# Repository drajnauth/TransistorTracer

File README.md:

# TransistorTracer
Hardware and software for transistor tracer project.

KiCad PCB files for various versions of the transistor tracer as well as PlatformIO files for the firmware for the Arduino Nano.
The documentation folder contains a pdf version of a PowerPoint presentation regarding the tracer as well as build and operation instructions

A presentation introducing the tracer can be found at https://youtu.be/t6_chWRdSyg.  
This video is a bit dated and some of the information regarding the build, calibration and usage may have changed.

Currently only Hardware version 1 is documented and is working. Other versions are experimental and has not been verified. The software for experimental board versions may not work.

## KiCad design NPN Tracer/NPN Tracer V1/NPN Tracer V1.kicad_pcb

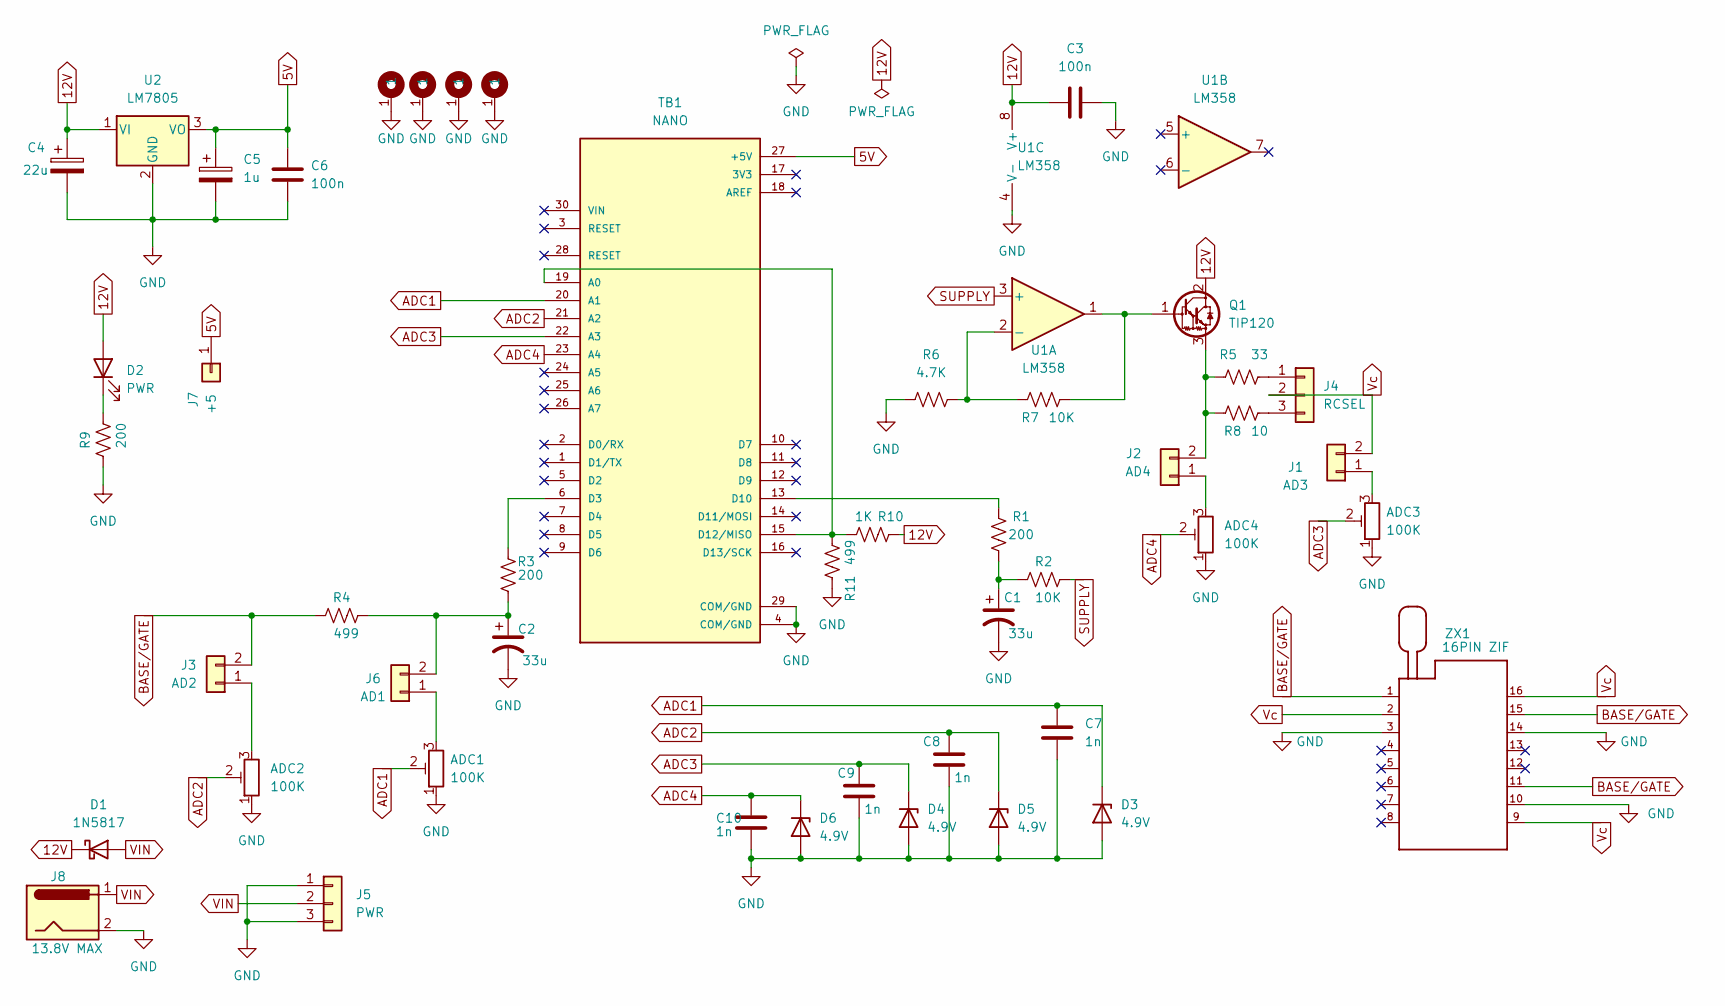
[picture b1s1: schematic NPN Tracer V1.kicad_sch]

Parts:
ADC1, ADC2, ADC3, ADC4: 100K; Potentiometer_Bourns_3296W_Vertical
C1, C2: 33u; CP_Radial_D8.0mm_P2.50mm
C3: 100n; C_1206_3216Metric_Pad1.33x1.80mm_HandSolder
C4: 22u; CP_Radial_D8.0mm_P2.50mm
C5: 1u; CP_Radial_D8.0mm_P2.50mm
C6: 100n; C_1206_3216Metric
C7, C8, C9, C10: 1n; C_1206_3216Metric
D1: 1N5817; D_DO-41_SOD81_P10.16mm_Horizontal
D2: PWR; LED_D3.0mm
D3, D4, D5, D6: 4.9V; D_SOD-323
H1, H2, H3, H4: MountingHole; MountingHole_3.2mm_M3_ISO7380_Pad_TopBottom
J1: AD3; PinHeader_1x02_P2.54mm_Vertical
J2: AD4; PinHeader_1x02_P2.54mm_Vertical
J3: AD2; PinHeader_1x02_P2.54mm_Vertical
J4: RCSEL; PinHeader_1x03_P2.54mm_Vertical
J5: PWR; PinHeader_1x03_P2.54mm_Vertical
J6: AD1; PinHeader_1x02_P2.54mm_Vertical
J7: +5; PinHeader_1x01_P2.54mm_Vertical
J8: 13.8V MAX; BarrelJack_GCT_DCJ200-10-A_Horizontal
Q1: TIP120; TO-220-3_Vertical
R1, R3: 200; R_Axial_DIN0204_L3.6mm_D1.6mm_P5.08mm_Vertical
R2, R7: 10K; R_1206_3216Metric_Pad1.30x1.75mm_HandSolder
R4: 499; R_Axial_DIN0204_L3.6mm_D1.6mm_P5.08mm_Vertical
R5: 33; R_Axial_DIN0516_L15.5mm_D5.0mm_P7.62mm_Vertical
R6: 4.7K; R_1206_3216Metric_Pad1.30x1.75mm_HandSolder
R8: 10; R_Axial_DIN0516_L15.5mm_D5.0mm_P7.62mm_Vertical
R9: 200; R_1206_3216Metric_Pad1.30x1.75mm_HandSolder
R10: 1K; R_1206_3216Metric_Pad1.30x1.75mm_HandSolder
R11: 499; R_1206_3216Metric_Pad1.30x1.75mm_HandSolder
TB1: NANO; SHIELD_ARDUINO_NANO
U1: LM358; DIP-8_W7.62mm_Socket
U2: LM7805; TO-220-3_Vertical
ZX1: 16PIN ZIF; 16Pin ZIF; MPN 216-3340-00-0602J

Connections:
5V: C5.1, C6.1, J7.1, TB1.27 (+5V), U2.3 (VO)
12V: C3.1, C4.1, D1.1 (K), D2.2 (A), Q1.2 (C), R10.2, U1.8 (V+), U2.1 (VI)
ADC1: ADC1.2, C7.1, D3.1 (K), TB1.20 (A1)
ADC2: ADC2.2, C8.1, D5.1 (K), TB1.21 (A2)
ADC3: ADC3.2, C9.1, D4.1 (K), TB1.22 (A3)
ADC4: ADC4.2, C10.1, D6.1 (K), TB1.23 (A4)
BASE/GATE: J3.2, R4.1, ZX1.1, ZX1.11, ZX1.15
GND: ADC1.1, ADC2.1, ADC3.1, ADC4.1, C1.2, C2.2, C3.2, C4.2, C5.2, C6.2, C7.2, C8.2, C9.2, C10.2, D3.2 (A), D4.2 (A), D5.2 (A), D6.2 (A), H1.1, H2.1, H3.1, H4.1, J5.1, J5.3, J8.2, R6.1, R9.1, R11.2, TB1.4 (COM/GND), TB1.29 (COM/GND), U1.4 (V-), U2.2 (GND), ZX1.3, ZX1.10, ZX1.14
unnamed: ADC1.3, J6.1
unnamed: ADC2.3, J3.1
unnamed: ADC3.3, J1.1
unnamed: ADC4.3, J2.1
unnamed: C1.1, R1.1, R2.1
unnamed: C2.1, J6.2, R3.1, R4.2
unnamed: D2.1 (K), R9.2
unnamed: J2.2, Q1.3 (E), R5.1, R8.1
unnamed: J4.1, R5.2
unnamed: J4.3, R8.2
unnamed: Q1.1 (B), R7.2, U1.1
unnamed: R1.2, TB1.13 (D10)
unnamed: R3.2, TB1.6 (D3)
unnamed: R6.2, R7.1, U1.2 (-)
unnamed: R10.1, R11.1, TB1.15 (D12/MISO), TB1.19 (A0)
SUPPLY: R2.2, U1.3 (+)
VIN: D1.2 (A), J5.2, J8.1
Vc: J1.2, J4.2, ZX1.2, ZX1.9, ZX1.16

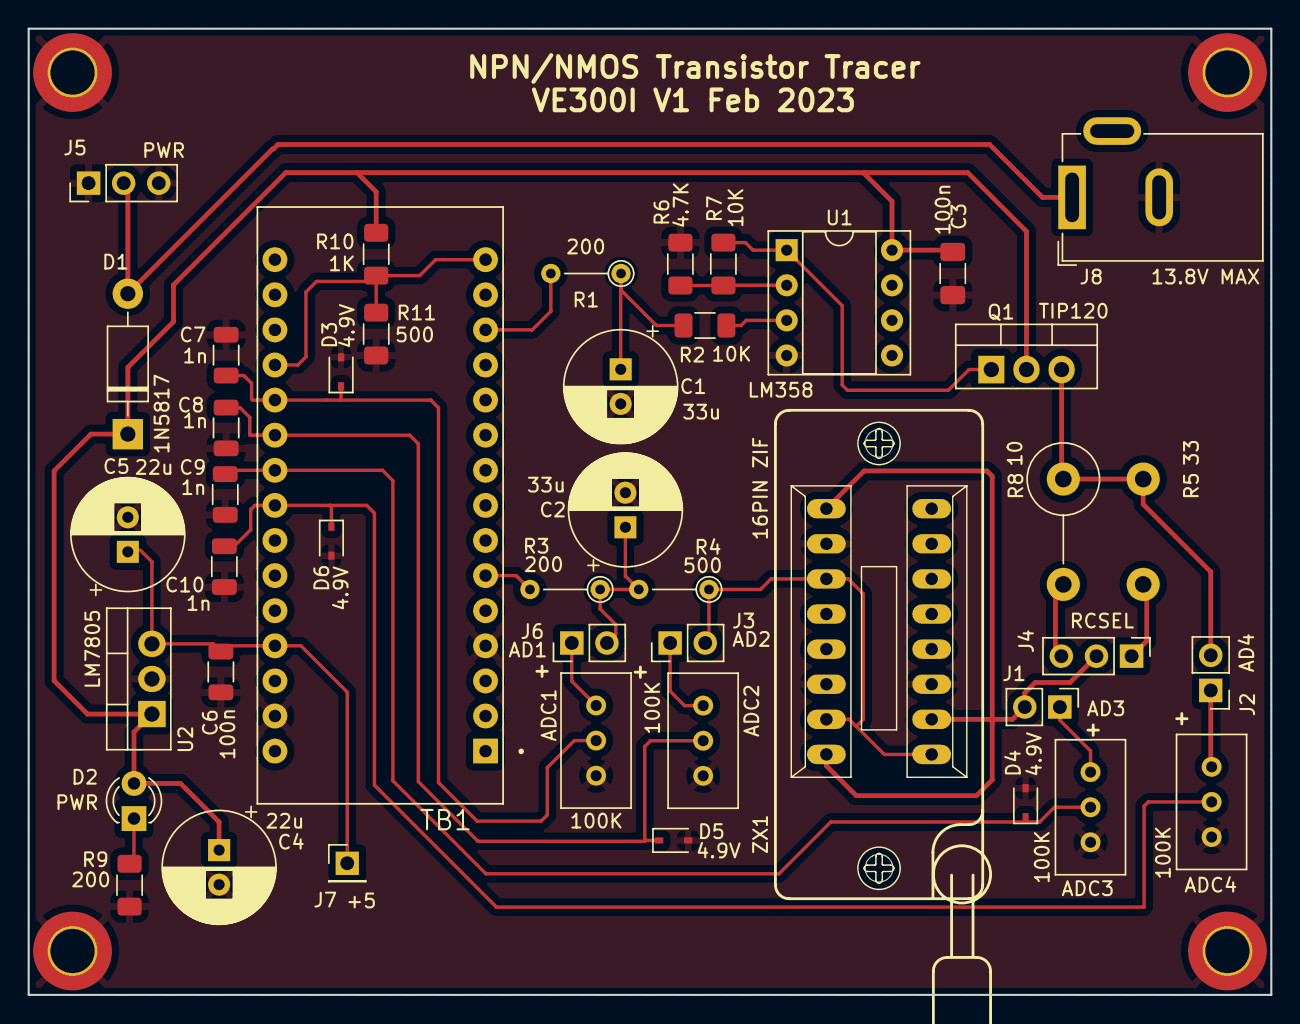
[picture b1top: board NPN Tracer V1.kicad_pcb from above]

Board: 2 copper layers, 89.9 x 69.9 mm, 48 parts (1 on the bottom side), 26 nets.

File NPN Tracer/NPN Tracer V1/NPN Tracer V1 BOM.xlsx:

Component Count: | 44 |  |  | Note: Many of the resistor values can be changed except for PWM resistors (R1 &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
Ref | Qnty | Value | Cmp name | Notes | Footprint | Description | Vendor
ADC1, ADC2, ADC3, ADC4, | 4 | 10K | R_Potentiometer_Trim | Error. Use 100K Pots | Potentiometer_THT:Potentiometer_Bourns_3296W_Vertical | Trim-potentiometer
C1, C2, | 2 | 33u | C_Polarized_US |  | Capacitor_THT:CP_Radial_D8.0mm_P2.50mm | Polarized capacitor, US symbol
C3, | 1 | 100n | C |  | Capacitor_SMD:C_1206_3216Metric_Pad1.33x1.80mm_HandSolder | Unpolarized capacitor
C4, | 1 | 22u | C_Polarized | This is for voltage regulator. Anything around 10 or 20uF is adaquate. | Capacitor_THT:CP_Radial_D8.0mm_P2.50mm | Polarized capacitor
C4 | 1 | 1u | C_Polarized | This is for voltage regulator. Anything around 1uF is adaquate. | Capacitor_THT:CP_Radial_D8.0mm_P2.50mm | Polarized capacitor
C6, | 1 | 100n | C |  | Capacitor_SMD:C_1206_3216Metric | Unpolarized capacitor
C7, C8, C9, C10, | 4 | 1n | C | Optional. Used to reduce noise on ADC line. If ADC values are noisy, then add c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 | Capacitor_SMD:C_1206_3216Metric | Unpolarized capacitor
D1, | 1 | 1N5817 | 1N5817 | Use any Shottky Diode with low voltage drop and high current. Need about 1-2A | Diode_THT:D_DO-41_SOD81_P10.16mm_Horizontal | 20V 1A Schottky Barrier Rectifier Diode, DO-41
D2, | 1 | PWR | LED | Use any LED with 3mm Footprint with max current of 60mA | LED_THT:LED_D3.0mm | Light emitting diode
D3, D4, D5, D6, | 4 | 4.9V | D_Zener | Optional. Can be omitted. Used to protect Arduino should >5V fed to ADC pins. | Diode_SMD:D_SOD-323 | Zener diode
J1, | 1 | AD3 | Conn_01x02 |  | Connector_PinHeader_2.54mm:PinHeader_1x02_P2.54mm_Vertical | Generic connector, single row, 01x02, script generated (kicad-library-utils/sch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
J2, | 1 | AD4 | Conn_01x02 |  | Connector_PinHeader_2.54mm:PinHeader_1x02_P2.54mm_Vertical | Generic connector, single row, 01x02, script generated (kicad-library-utils/sch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
J3, | 1 | AD2 | Conn_01x02 |  | Connector_PinHeader_2.54mm:PinHeader_1x02_P2.54mm_Vertical | Generic connector, single row, 01x02, script generated (kicad-library-utils/sch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
J4, | 1 | RCSEL | Conn_01x03 |  | Connector_PinHeader_2.54mm:PinHeader_1x03_P2.54mm_Vertical | Generic connector, single row, 01x03, script generated (kicad-library-utils/sch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
J5, | 1 | PWR | Conn_01x03 |  | Connector_PinHeader_2.54mm:PinHeader_1x03_P2.54mm_Vertical | Generic connector, single row, 01x03, script generated (kicad-library-utils/sch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
J6, | 1 | AD1 | Conn_01x02 |  | Connector_PinHeader_2.54mm:PinHeader_1x02_P2.54mm_Vertical | Generic connector, single row, 01x02, script generated (kicad-library-utils/sch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
J7, | 1 | 5 | Conn_01x01 |  | Connector_PinHeader_2.54mm:PinHeader_1x01_P2.54mm_Vertical | Generic connector, single row, 01x01, script generated (kicad-library-utils/sch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
J8, | 1 | 13.8V MAX | Barrel_Jack | J5/PWR connector can be used instead. Middle pin is power. | Connector_BarrelJack:BarrelJack_GCT_DCJ200-10-A_Horizontal | DC Barrel Jack
Q1, | 1 | TIP120 | TIP120 | Can use any high current transistor. TIP122, 2SC5706 with same TO-220 footprint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 | Package_TO_SOT_THT:TO-220-3_Vertical | 5A Ic, 60V Vce, Silicon Darlington Power NPN Transistor, TO-220
R1, R3, | 2 | 200 | R_US |  | Resistor_THT:R_Axial_DIN0204_L3.6mm_D1.6mm_P5.08mm_Vertical | Resistor, US symbol
R10, | 1 | 1K | R_US | Measure the actual value with VOM and enter it during calibration | Resistor_SMD:R_1206_3216Metric_Pad1.30x1.75mm_HandSolder | Resistor, US symbol
R11, | 1 | 499 | R_US | Anything below 523R and around 500R. E.g. 475, 487,499, 511, 523. Measure the a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 | Resistor_SMD:R_1206_3216Metric_Pad1.30x1.75mm_HandSolder | Resistor, US symbol
R2, R7, | 2 | 10K | R_US | R2 can be anything around 10K. R7 MUST be 10K | Resistor_SMD:R_1206_3216Metric_Pad1.30x1.75mm_HandSolder | Resistor, US symbol
R4, | 1 | 499 | R_US | Use resistor below 500R. I used 462. This limits how much current delivered to 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 | Resistor_THT:R_Axial_DIN0204_L3.6mm_D1.6mm_P5.08mm_Vertical | Resistor, US symbol
R5, | 1 | 33 | R_US | 2 Watt resistor. Measure the actual value with VOM and enter it during calibrat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 | Resistor_THT:R_Axial_DIN0516_L15.5mm_D5.0mm_P7.62mm_Vertical | Resistor, US symbol
R6, | 1 | 4.7K | R_US | This resistor sets the gain of the LM358. 4.7K seems to be ok. Might be a littl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 | Resistor_SMD:R_1206_3216Metric_Pad1.30x1.75mm_HandSolder | Resistor, US symbol
R8, | 1 | 10 | R_US | 2 Watt resistor. Measure the actual value with VOM and enter it during calibrat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 | Resistor_THT:R_Axial_DIN0516_L15.5mm_D5.0mm_P7.62mm_Vertical | Resistor, US symbol
R9, | 1 | 200 | R_US |  | Resistor_SMD:R_1206_3216Metric_Pad1.30x1.75mm_HandSolder | Resistor, US symbol
TB1, | 1 | NANO | ARDUINO_NANO |  | SHIELD_ARDUINO_NANO
U1, | 1 | LM358 | LM358 |  | Package_DIP:DIP-8_W7.62mm_Socket | Low-Power, Dual Operational Amplifiers, DIP-8/SOIC-8/TO-99-8
U2, | 1 | LM7805 | LM7805_TO220 |  | Package_TO_SOT_THT:TO-220-3_Vertical | Positive 1A 35V Linear Regulator, Fixed Output 5V, TO-220
ZX1, | 1 | 16PIN ZIF | 16Pin ZIF |  | Custom_RF:16Pin ZIF

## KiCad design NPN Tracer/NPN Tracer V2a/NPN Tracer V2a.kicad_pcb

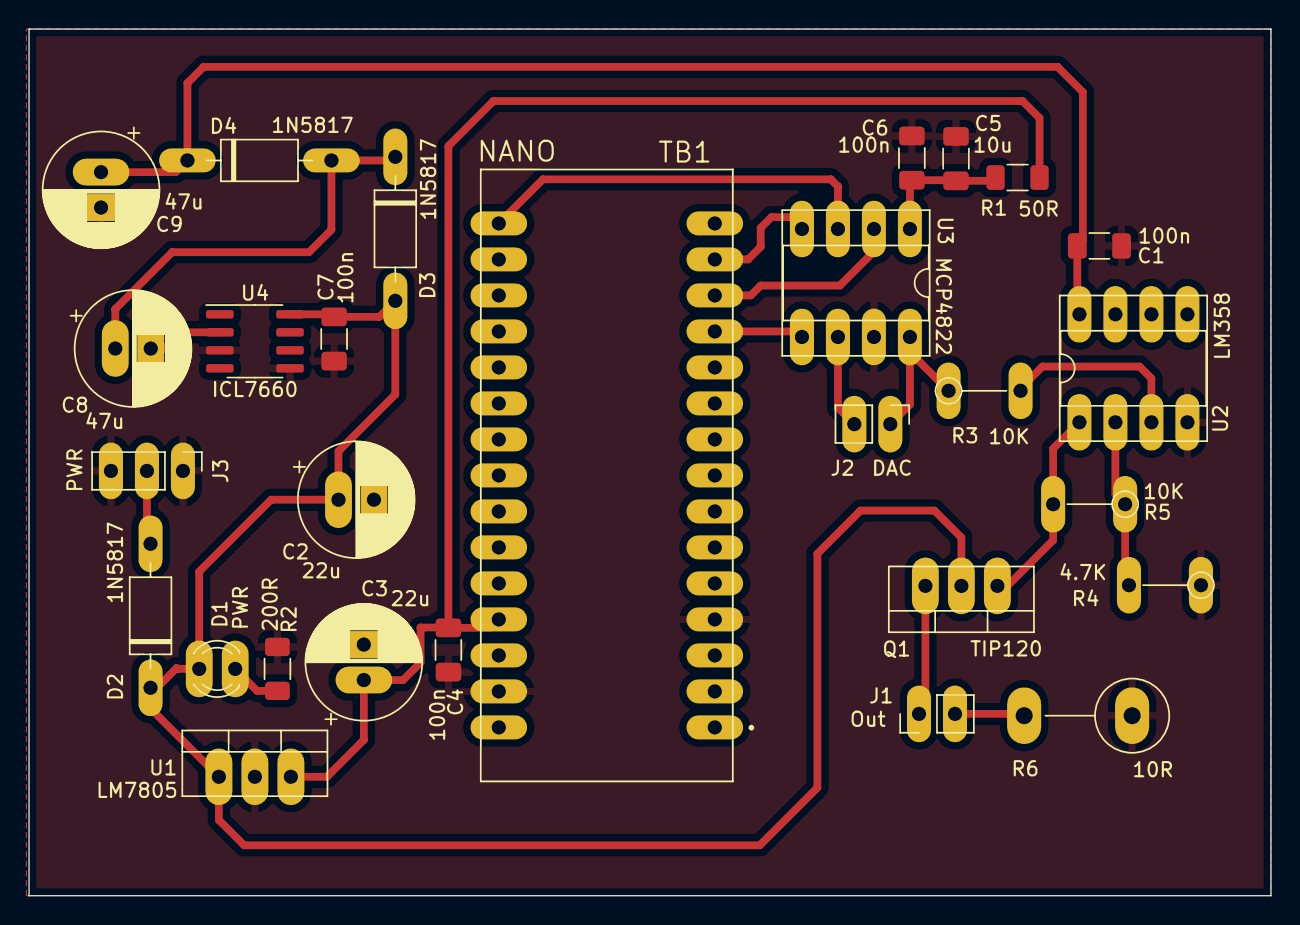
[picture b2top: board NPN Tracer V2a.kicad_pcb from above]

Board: 2 copper layers, 87.6 x 61.2 mm, 28 parts (0 on the bottom side), 20 nets.

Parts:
C1, C4, C6, C7: 100n; C_1206_3216Metric_Pad1.33x1.80mm_HandSolder
C2, C3: 22u; CP_Radial_D8.0mm_P2.50mm
C5: 10u; C_1206_3216Metric_Pad1.33x1.80mm_HandSolder
C8, C9: 47u; CP_Radial_D8.0mm_P2.50mm
D1: PWR; LED_D3.0mm
D2, D3, D4: 1N5817; D_DO-41_SOD81_P10.16mm_Horizontal
J1: Out; PinHeader_1x02_P2.54mm_Vertical
J2: DAC; PinHeader_1x02_P2.54mm_Vertical
J3: PWR; PinHeader_1x03_P2.54mm_Vertical
Q1: TIP120; TO-220-3_Vertical
R1: 50R; R_1206_3216Metric_Pad1.30x1.75mm_HandSolder
R2: 200R; R_1206_3216Metric_Pad1.30x1.75mm_HandSolder
R3, R5: 10K; R_Axial_DIN0204_L3.6mm_D1.6mm_P5.08mm_Vertical
R4: 4.7K; R_Axial_DIN0204_L3.6mm_D1.6mm_P5.08mm_Vertical
R6: 10R; R_Axial_DIN0516_L15.5mm_D5.0mm_P7.62mm_Vertical
TB1: NANO; SHIELD_ARDUINO_NANO
U1: LM7805; TO-220-3_Vertical
U2: LM358; DIP-8_W7.62mm_Socket
U3: MCP4822; DIP-8_W7.62mm_Socket
U4: ICL7660; SOIC-8_3.9x4.9mm_P1.27mm

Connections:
5V: C3.1, C4.2, R1.2, TB1.27 (+5V), U1.3 (VO)
12V: C2.1, C7.2, D1.2 (A), D2.1 (K), D3.2 (A), Q1.2 (C), U1.1 (VI), U4.8 (V+)
24V: C1.1, C9.1, D4.1 (K), U2.8 (V+)
GND: C1.2, C2.2, C3.2, C4.1, C5.1, C6.1, C7.1, C9.2, J3.1, J3.3, R2.1, R4.1, R6.1, TB1.4 (COM/GND), TB1.29 (COM/GND), U1.2 (GND), U2.4 (V-), U3.7 (Vss), U4.3 (GND), U4.5 (VOUT)
unnamed: C5.2, C6.2, R1.1, U3.1 (Vdd)
unnamed: C8.1, D3.1 (K), D4.2 (A)
unnamed: C8.2, U4.2 (CAP+)
unnamed: D1.1 (K), R2.2
unnamed: J1.1, Q1.3 (E)
unnamed: J1.2, R6.2
unnamed: J2.1, R3.1, U3.8 (VA)
unnamed: J2.2, U3.6 (VB)
unnamed: Q1.1 (B), R5.2, U2.1
unnamed: R3.2, U2.3 (+)
unnamed: R4.2, R5.1, U2.2 (-)
unnamed: TB1.12 (D9), U3.5 (~LDAC)
unnamed: TB1.13 (D10), U3.2 (~CS)
unnamed: TB1.14 (D11/MOSI), U3.4 (SDI)
unnamed: TB1.16 (D13/SCK), U3.3 (SCK)
VIN: D2.2 (A), J3.2

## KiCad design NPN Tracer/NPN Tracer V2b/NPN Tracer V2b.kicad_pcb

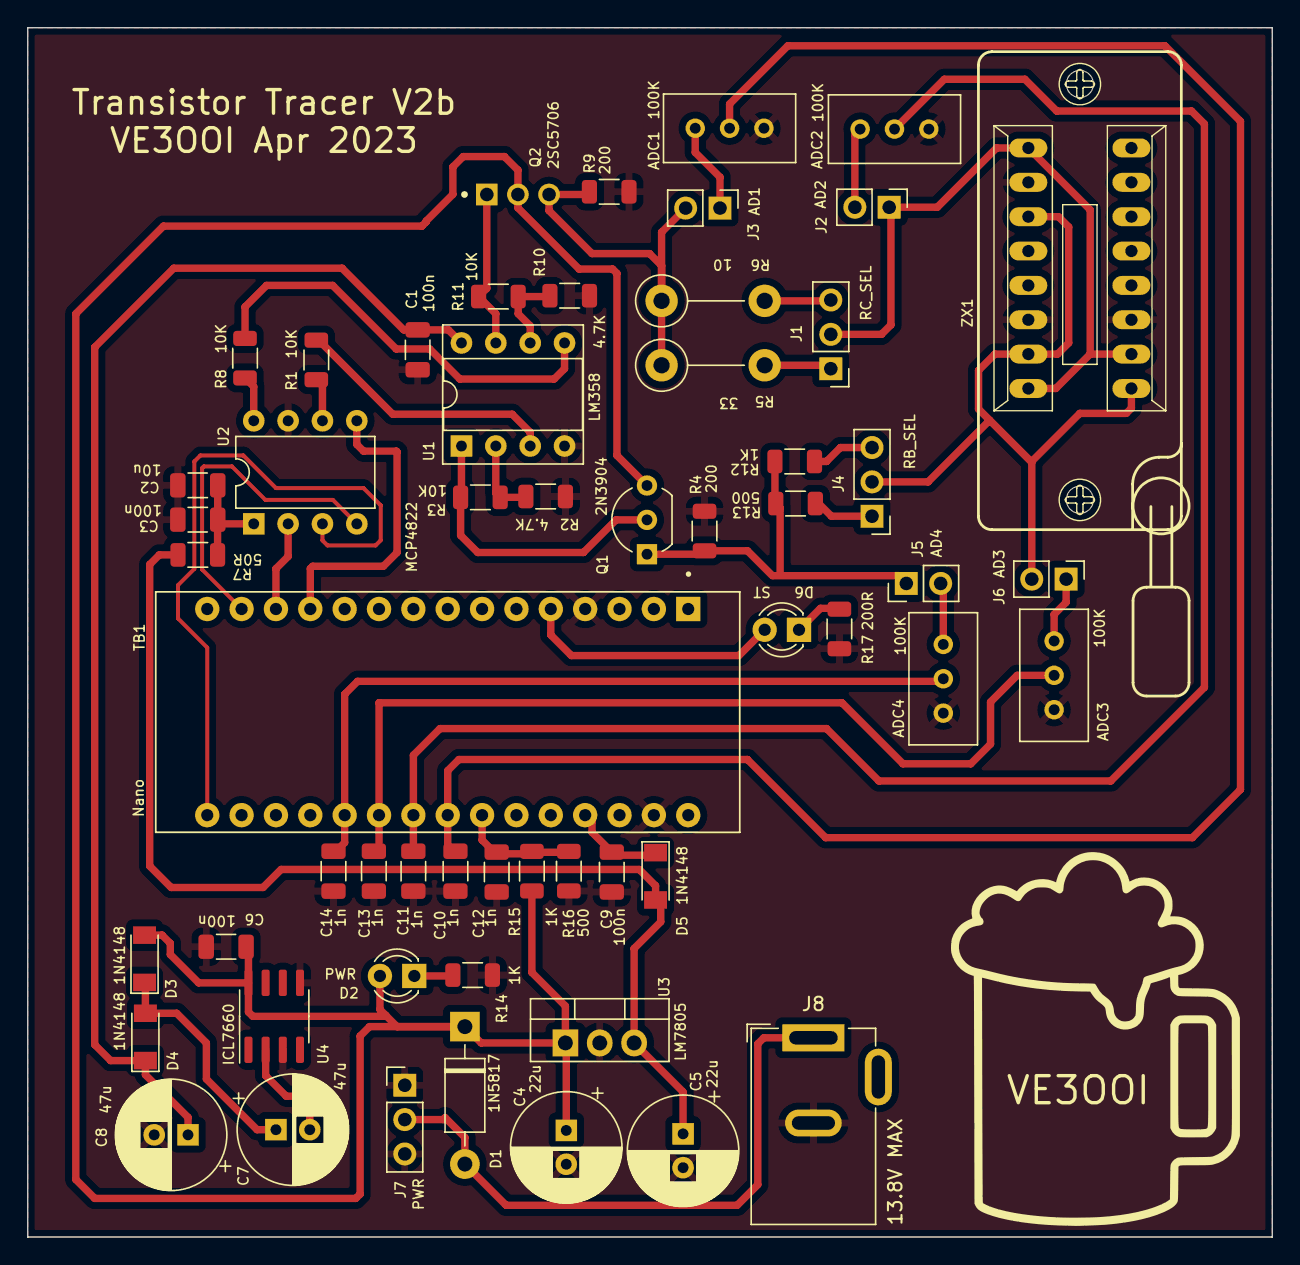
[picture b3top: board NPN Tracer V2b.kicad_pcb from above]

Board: 2 copper layers, 92.0 x 89.4 mm, 57 parts (0 on the bottom side), 41 nets.

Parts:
ADC1, ADC2, ADC3, ADC4: 100K; Potentiometer_Bourns_3296W_Vertical
C1, C3, C6, C9: 100n; C_1206_3216Metric
C2: 10u; C_1206_3216Metric
C4, C5: 22u; CP_Radial_D8.0mm_P2.50mm
C7, C8: 47u; CP_Radial_D8.0mm_P2.50mm
C10, C11, C12, C13, C14: 1n; C_1206_3216Metric
D1: 1N5817; D_DO-41_SOD81_P10.16mm_Horizontal
D2: PWR; LED_D3.0mm
D3, D4, D5: 1N4148; D_MiniMELF
D6: ST; LED_D3.0mm
J1: RC_SEL; PinHeader_1x03_P2.54mm_Vertical
J2: AD2; PinHeader_1x02_P2.54mm_Vertical
J3: AD1; PinHeader_1x02_P2.54mm_Vertical
J4: RB_SEL; PinHeader_1x03_P2.54mm_Vertical
J5: AD4; PinHeader_1x02_P2.54mm_Vertical
J6: AD3; PinHeader_1x02_P2.54mm_Vertical
J7: PWR; PinHeader_1x03_P2.54mm_Vertical
J8: 13.8V MAX; BarrelJack_GCT_DCJ200-10-A_Horizontal
Q1: 2N3904; TO-92_Inline_Wide
Q2: 2SC5706
R1, R3, R8, R11: 10K; R_1206_3216Metric
R2, R10: 4.7K; R_1206_3216Metric
R4, R9: 200; R_1206_3216Metric
R5: 33; R_Axial_DIN0411_L9.9mm_D3.6mm_P7.62mm_Vertical
R6: 10; R_Axial_DIN0411_L9.9mm_D3.6mm_P7.62mm_Vertical
R7: 50R; R_1206_3216Metric
R12, R14, R15: 1K; R_1206_3216Metric
R13, R16: 500; R_1206_3216Metric
R17: 200R; R_1206_3216Metric
TB1: Nano; SHIELD_ARDUINO_NANO
U1: LM358; DIP-8_W7.62mm_Socket
U2: MCP4822; DIP-8_W7.62mm
U3: LM7805; TO-220-3_Vertical
U4: ICL7660; SOIC-8_3.9x4.9mm_P1.27mm
ZX1: 16PIN ZIF; 16Pin ZIF

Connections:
5V: C5.1, D5.2 (A), R7.2, U3.3 (VO)
12V: C4.1, C6.2, D1.1 (K), D2.2 (A), D3.2 (A), Q1.3 (C), Q2.2 (C), R15.2, U3.1 (VI), U4.8 (V+)
24V: C1.1, C8.1, D4.1 (K), U1.8 (V+)
ADC1: ADC4.2, C14.1, TB1.20 (A1)
ADC2: ADC3.2, C13.1, TB1.21 (A2)
ADC3: ADC2.2, C11.1, TB1.22 (A3)
ADC4: ADC1.2, C10.1, TB1.23 (A4)
BASE/GATE: J4.2, J6.2, ZX1.1, ZX1.11, ZX1.15
COLLECTOR/DRAIN: J1.2, J2.1, ZX1.2, ZX1.9, ZX1.16
CS: TB1.13 (D10), U2.2 (~CS)
DacPower: C2.2, C3.2, R7.1, U2.1 (Vdd)
GND: ADC1.1, ADC2.1, ADC3.1, ADC4.1, C1.2, C2.1, C3.1, C4.2, C5.2, C6.1, C8.2, C9.2, C10.2, C11.2, C12.2, C13.2, C14.2, J7.1, J7.3, J8.2, R2.1, R4.1, R9.1, R10.1, R14.1, R16.2, R17.1, TB1.4 (COM/GND), TB1.29 (COM/GND), U1.4 (V-), U2.7 (Vss), U3.2 (GND), U4.3 (GND), U4.5 (VOUT), ZX1.3, ZX1.10, ZX1.14
LDAC: TB1.12 (D9), U2.5 (~LDAC)
unnamed: ADC1.3, J3.1
unnamed: ADC2.3, J2.2
unnamed: ADC3.3, J6.1
unnamed: ADC4.3, J5.2
unnamed: C7.1, D3.1 (K), D4.2 (A)
unnamed: C7.2, U4.2 (CAP+)
unnamed: C12.1, R15.1, R16.1, TB1.24 (A5)
unnamed: D2.1 (K), R14.2
unnamed: D6.1 (K), R17.2
unnamed: D6.2 (A), TB1.5 (D2)
unnamed: J1.1, R5.2
unnamed: J1.3, R6.2
unnamed: J4.1, R13.1
unnamed: J4.3, R12.1
unnamed: Q1.2 (B), R3.2, U1.1
unnamed: Q2.1 (B), R11.2, U1.7
unnamed: R1.1, U2.6 (VB)
unnamed: R1.2, U1.3 (+)
unnamed: R2.2, R3.1, U1.2 (-)
unnamed: R8.1, U2.8 (VA)
unnamed: R8.2, U1.5 (+)
unnamed: R10.2, R11.1, U1.6 (-)
SCK: TB1.16 (D13/SCK), U2.3 (SCK)
SDI: TB1.14 (D11/MOSI), U2.4 (SDI)
VB_OUT: J5.1, Q1.1 (E), R4.2, R12.2, R13.2
VC_OUT: J3.2, Q2.3 (E), R5.1, R6.1, R9.2
VIN: D1.2 (A), J7.2, J8.1
uCPower: C9.1, D5.1 (K), TB1.27 (+5V)

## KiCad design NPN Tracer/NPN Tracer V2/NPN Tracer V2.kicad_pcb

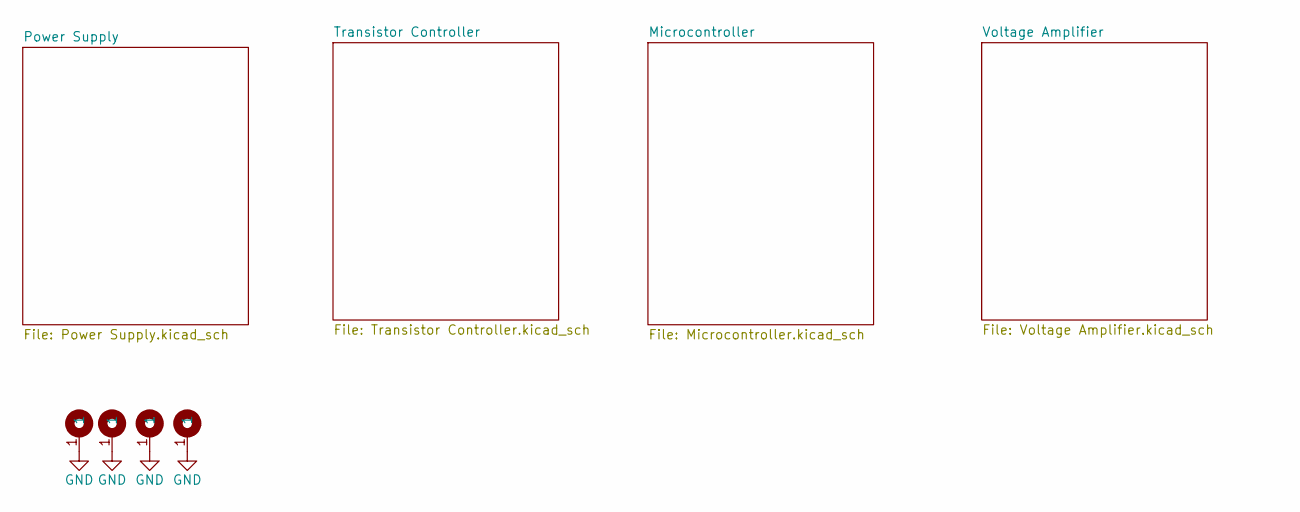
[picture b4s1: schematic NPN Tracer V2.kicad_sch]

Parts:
H1, H2, H3, H4: MountingHole; MountingHole_3.2mm_M3_ISO7380_Pad_TopBottom

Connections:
GND: H1.1, H2.1, H3.1, H4.1; also elsewhere on the board

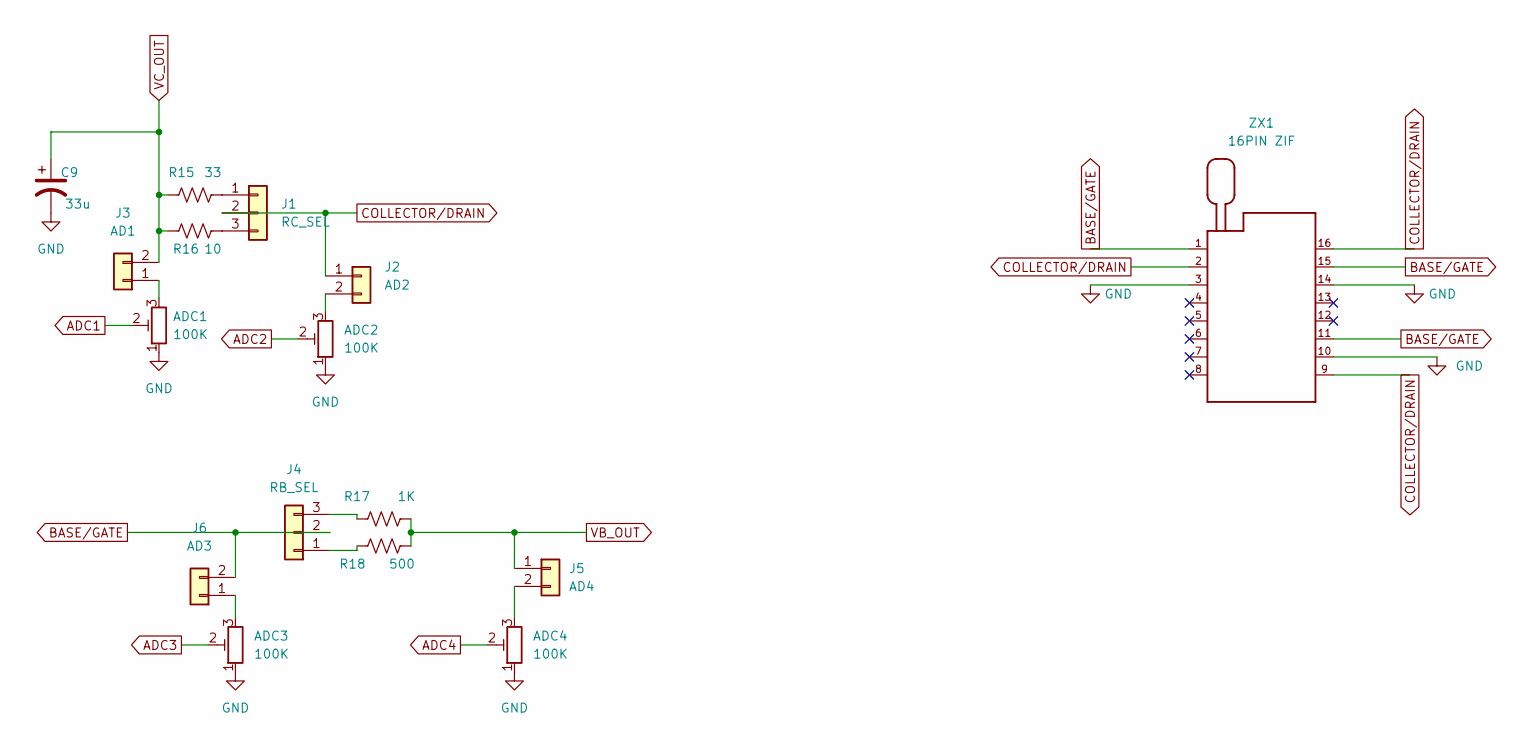
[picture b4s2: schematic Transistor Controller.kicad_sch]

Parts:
ADC1, ADC2, ADC3, ADC4: 100K; Potentiometer_Bourns_3296W_Vertical
C9: 33u; CP_Radial_D8.0mm_P2.50mm
J1: RC_SEL; PinHeader_1x03_P2.54mm_Vertical
J2: AD2; PinHeader_1x02_P2.54mm_Vertical
J3: AD1; PinHeader_1x02_P2.54mm_Vertical
J4: RB_SEL; PinHeader_1x03_P2.54mm_Vertical
J5: AD4; PinHeader_1x02_P2.54mm_Vertical
J6: AD3; PinHeader_1x02_P2.54mm_Vertical
R15: 33; R_Axial_DIN0411_L9.9mm_D3.6mm_P7.62mm_Vertical
R16: 10; R_Axial_DIN0411_L9.9mm_D3.6mm_P7.62mm_Vertical
R17: 1K; R_1206_3216Metric
R18: 500; R_1206_3216Metric
ZX1: 16PIN ZIF; 16Pin ZIF; MPN 216-3340-00-0602J

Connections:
ADC1: ADC1.2; also elsewhere on the board
ADC2: ADC2.2; also elsewhere on the board
ADC3: ADC3.2; also elsewhere on the board
ADC4: ADC4.2; also elsewhere on the board
BASE/GATE: J4.2, J6.2, ZX1.1, ZX1.11, ZX1.15
COLLECTOR/DRAIN: J1.2, J2.1, ZX1.2, ZX1.9, ZX1.16
GND: ADC1.1, ADC2.1, ADC3.1, ADC4.1, C9.2, ZX1.3, ZX1.10, ZX1.14; also elsewhere on the board
unnamed: ADC1.3, J3.1
unnamed: ADC2.3, J2.2
unnamed: ADC3.3, J6.1
unnamed: ADC4.3, J5.2
unnamed: J1.1, R15.2
unnamed: J1.3, R16.2
unnamed: J4.1, R18.1
unnamed: J4.3, R17.1
VB_OUT: J5.1, R17.2, R18.2; also elsewhere on the board
VC_OUT: C9.1, J3.2, R15.1, R16.1; also elsewhere on the board

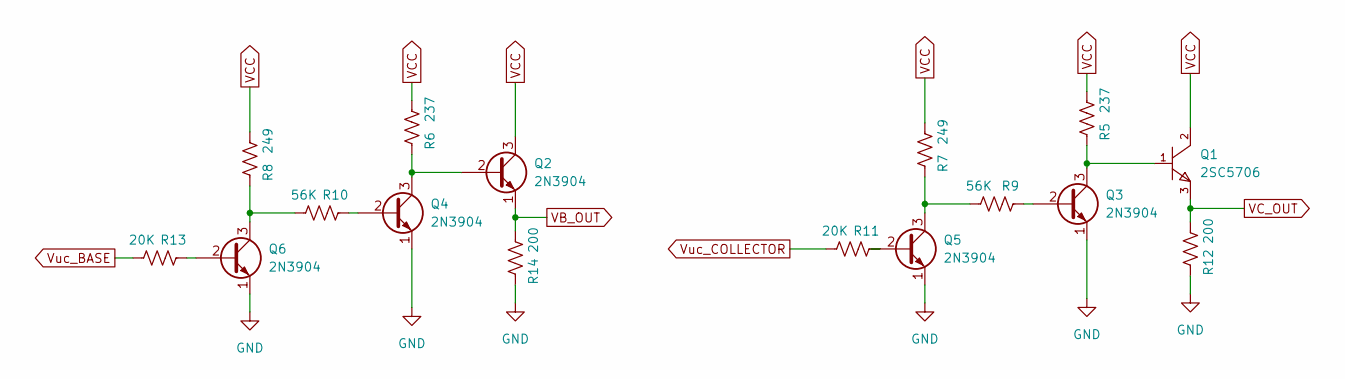
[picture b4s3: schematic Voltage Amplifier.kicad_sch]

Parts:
Q1: 2SC5706
Q2, Q3, Q4, Q5, Q6: 2N3904; TO-92_Inline
R5, R6: 237; R_1206_3216Metric
R7, R8: 249; R_1206_3216Metric
R9, R10: 56K; R_1206_3216Metric
R11, R13: 20K; R_1206_3216Metric
R12, R14: 200; R_1206_3216Metric

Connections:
GND: Q3.1 (E), Q4.1 (E), Q5.1 (E), Q6.1 (E), R12.1, R14.1; also elsewhere on the board
unnamed: Q1.1 (B), Q3.3 (C), R5.1
unnamed: Q2.2 (B), Q4.3 (C), R6.1
unnamed: Q3.2 (B), R9.1
unnamed: Q4.2 (B), R10.1
unnamed: Q5.2 (B), R11.1
unnamed: Q5.3 (C), R7.1, R9.2
unnamed: Q6.2 (B), R13.1
unnamed: Q6.3 (C), R8.1, R10.2
VB_OUT: Q2.1 (E), R14.2; also elsewhere on the board
VCC: Q1.2 (C), Q2.3 (C), R5.2, R6.2, R7.2, R8.2; also elsewhere on the board
VC_OUT: Q1.3 (E), R12.2; also elsewhere on the board
Vuc_BASE: R13.2; also elsewhere on the board
Vuc_COLLECTOR: R11.2; also elsewhere on the board

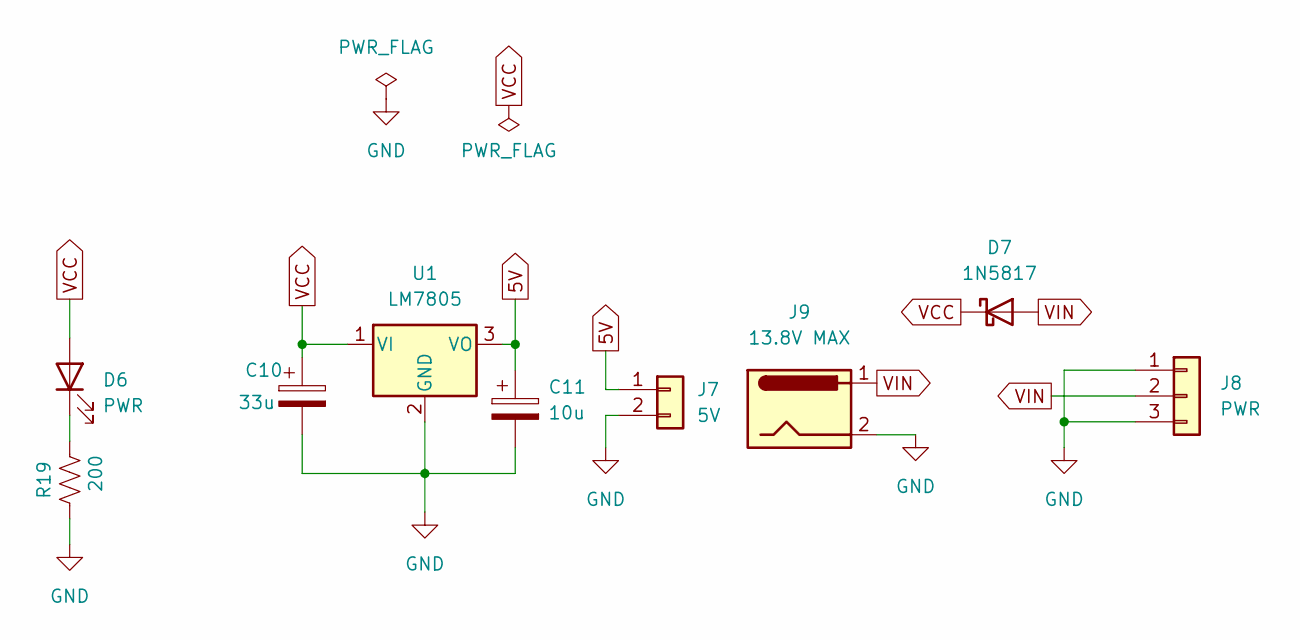
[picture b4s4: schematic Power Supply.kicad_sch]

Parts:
C10: 33u; CP_Radial_D8.0mm_P2.50mm
C11: 10u; CP_Radial_D8.0mm_P2.50mm
D6: PWR; LED_D3.0mm
D7: 1N5817; D_DO-41_SOD81_P10.16mm_Horizontal
J7: 5V; PinHeader_1x02_P2.54mm_Vertical
J8: PWR; PinHeader_1x03_P2.54mm_Vertical
J9: 13.8V MAX; BarrelJack_GCT_DCJ200-10-A_Horizontal
R19: 200; R_1206_3216Metric
U1: LM7805; TO-220-3_Vertical

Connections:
5V: C11.1, J7.1, U1.3 (VO); also elsewhere on the board
GND: C10.2, C11.2, J7.2, J8.1, J8.3, J9.2, R19.1, U1.2 (GND); also elsewhere on the board
unnamed: D6.1 (K), R19.2
VCC: C10.1, D6.2 (A), D7.1 (K), U1.1 (VI); also elsewhere on the board
VIN: D7.2 (A), J8.2, J9.1

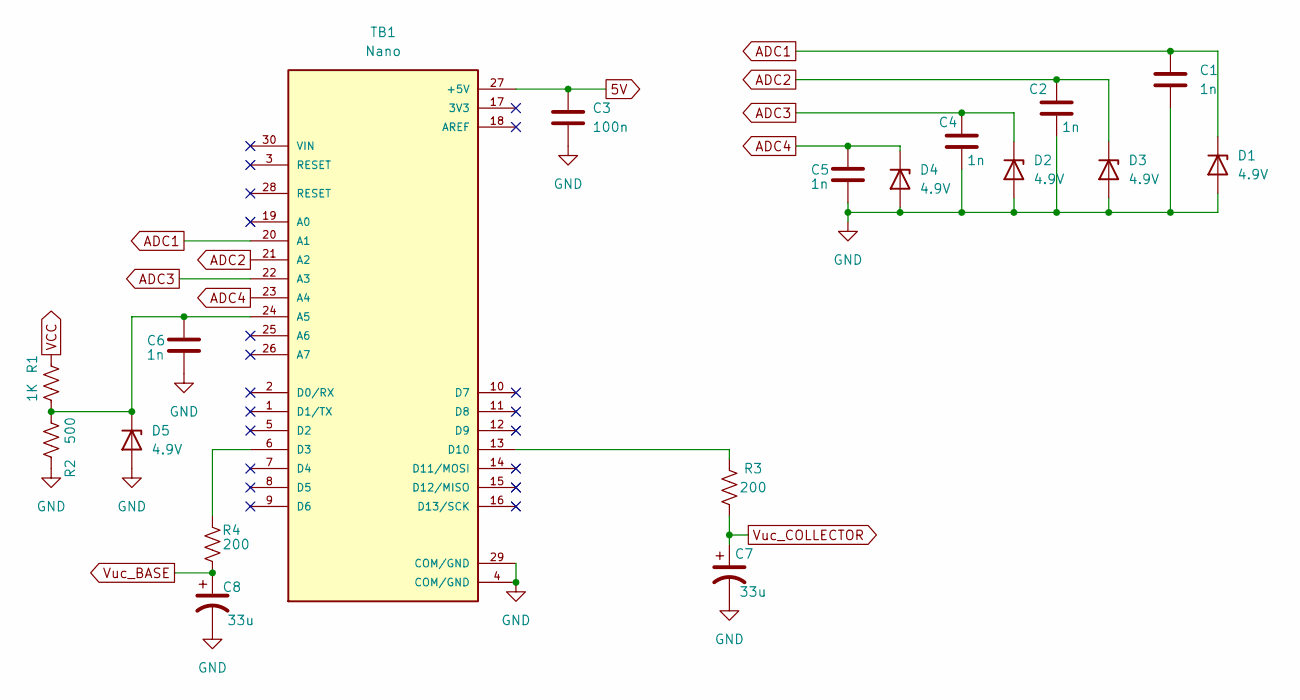
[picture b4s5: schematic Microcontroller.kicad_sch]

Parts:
C1, C2, C4, C5, C6: 1n; C_1206_3216Metric
C3: 100n; C_1206_3216Metric
C7, C8: 33u; CP_Radial_D8.0mm_P2.50mm
D1, D2, D3, D4, D5: 4.9V; D_SOD-323
R1: 1K; R_1206_3216Metric
R2: 500; R_1206_3216Metric
R3, R4: 200; R_1206_3216Metric
TB1: Nano; SHIELD_ARDUINO_NANO

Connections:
5V: C3.1, TB1.27 (+5V); also elsewhere on the board
ADC1: C1.1, D1.1 (K), TB1.20 (A1); also elsewhere on the board
ADC2: C2.1, D3.1 (K), TB1.21 (A2); also elsewhere on the board
ADC3: C4.1, D2.1 (K), TB1.22 (A3); also elsewhere on the board
ADC4: C5.1, D4.1 (K), TB1.23 (A4); also elsewhere on the board
GND: C1.2, C2.2, C3.2, C4.2, C5.2, C6.2, C7.2, C8.2, D1.2 (A), D2.2 (A), D3.2 (A), D4.2 (A), D5.2 (A), R2.2, TB1.4 (COM/GND), TB1.29 (COM/GND); also elsewhere on the board
unnamed: C6.1, D5.1 (K), R1.1, R2.1, TB1.24 (A5)
unnamed: R3.2, TB1.13 (D10)
unnamed: R4.2, TB1.6 (D3)
VCC: R1.2; also elsewhere on the board
Vuc_BASE: C8.1, R4.1; also elsewhere on the board
Vuc_COLLECTOR: C7.1, R3.1; also elsewhere on the board
